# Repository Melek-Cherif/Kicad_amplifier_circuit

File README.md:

# Kicad_amplifier_circuit
 This repo contains a kicad project, which is also the assignement of Hardware design for Raspberry Pi course  from coursera

<div style="text-align: center;">
    
<div>

<div style="text-align: center;">
    
<div>

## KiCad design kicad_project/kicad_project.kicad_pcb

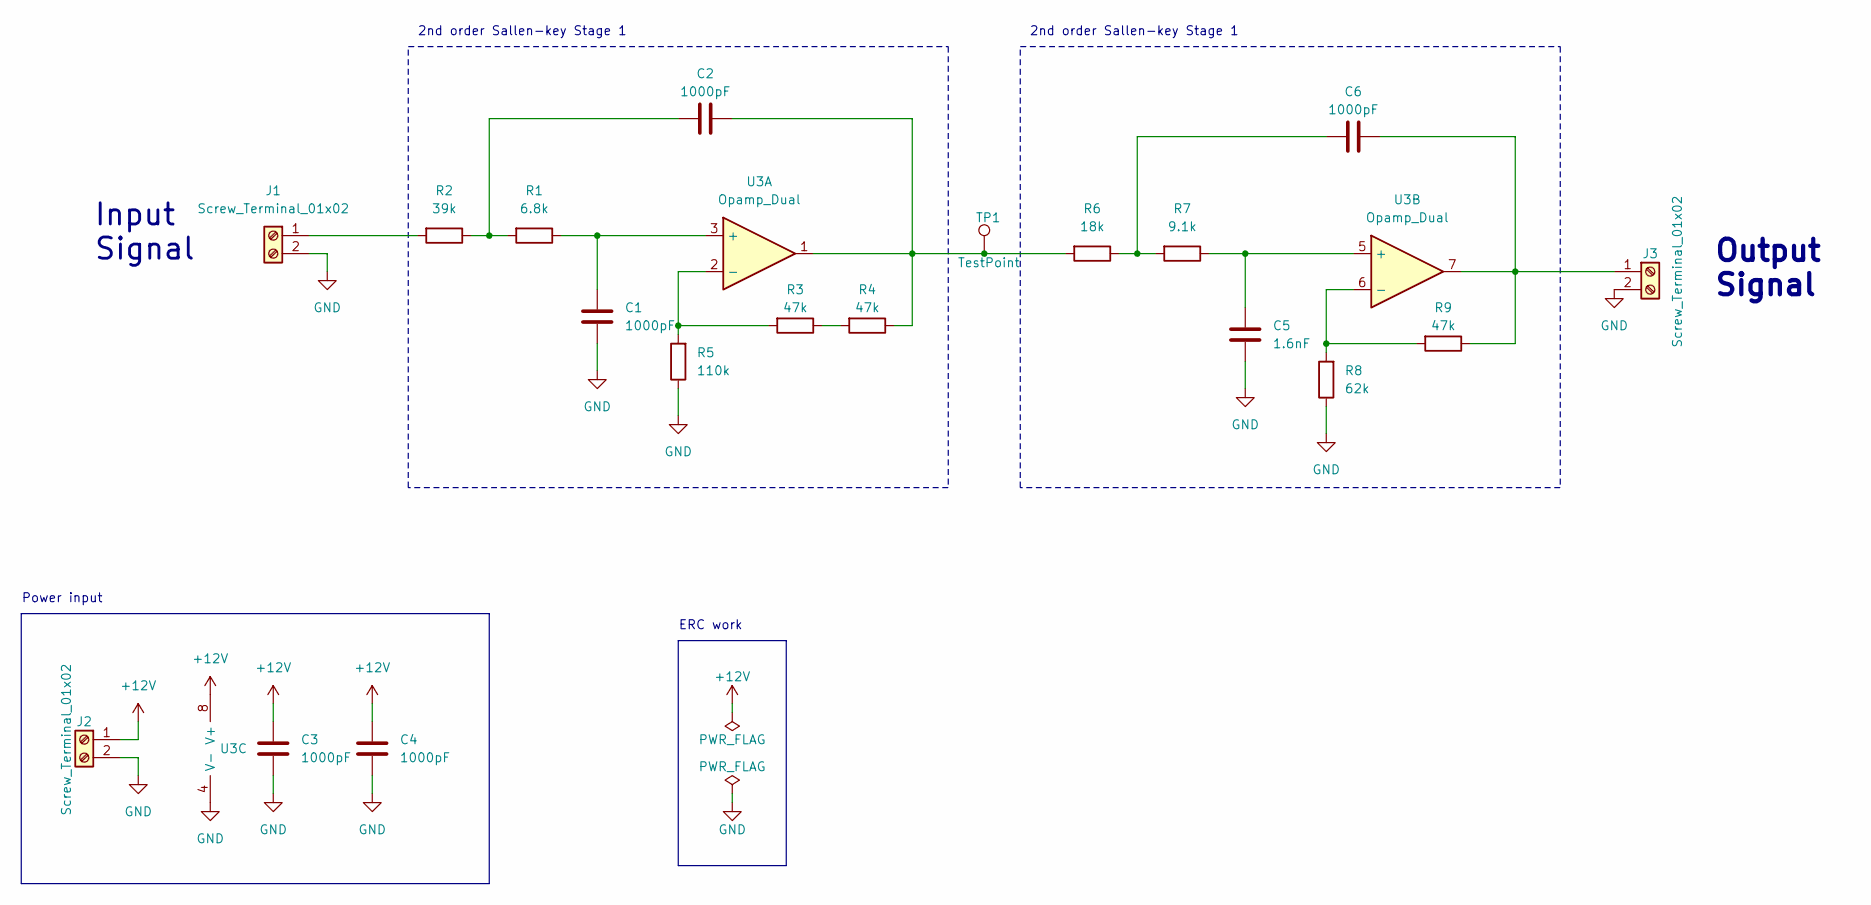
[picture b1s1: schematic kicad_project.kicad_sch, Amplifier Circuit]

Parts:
C1, C2, C3, C4, C6: 1000pF; CP_Radial_D4.0mm_P2.00mm
C5: 1.6nF; CP_Radial_D4.0mm_P2.00mm
J1, J2, J3: Screw_Terminal_01x02; PinHeader_1x02_P1.27mm_Vertical
R1: 6.8k; R_0402_1005Metric
R2: 39k; R_0402_1005Metric
R3, R4, R9: 47k; R_0402_1005Metric
R5: 110k; R_0402_1005Metric
R6: 18k; R_0402_1005Metric
R7: 9.1k; R_0402_1005Metric
R8: 62k; R_0402_1005Metric
TP1: TestPoint; TestPoint_Pad_2.0x2.0mm
U3: Opamp_Dual; DIP-8_W7.62mm

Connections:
+12V: C3.1, C4.1, J2.1, U3.8 (V+)
GND: C1.2, C3.2, C4.2, C5.2, J1.2, J2.2, J3.2, R5.1, R8.1, U3.4 (V-)
unnamed: C2.1, R4.1, R6.2, TP1.1, U3.1
unnamed: C2.2, R1.2, R2.1
unnamed: C6.2, R6.1, R7.2
unnamed: J1.1, R2.2
unnamed: C6.1, J3.1, R9.1, U3.7
unnamed: R3.1, R4.2
unnamed: C1.1, R1.1, U3.3 (+)
unnamed: R3.2, R5.2, U3.2 (-)
unnamed: C5.1, R7.1, U3.5 (+)
unnamed: R8.2, R9.2, U3.6 (-)

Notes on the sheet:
ERC work
2nd order Sallen-key Stage 1
Input Signal
Power input
Output Signal

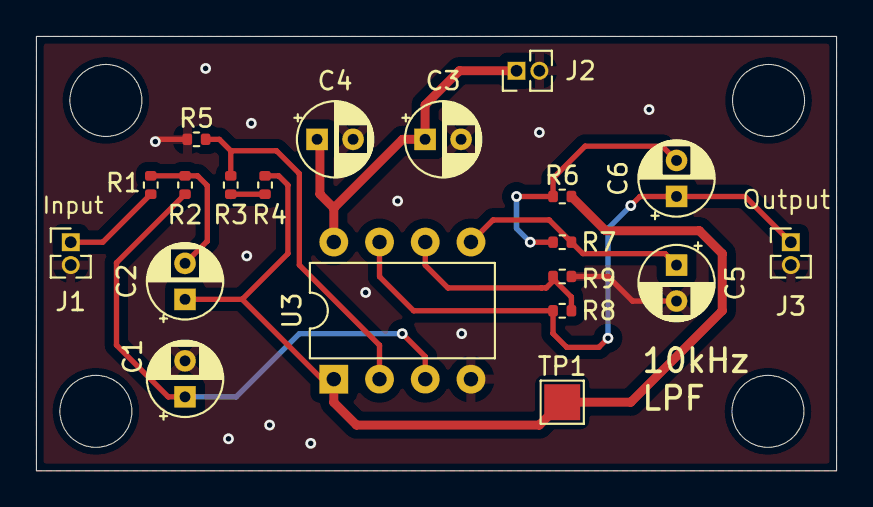
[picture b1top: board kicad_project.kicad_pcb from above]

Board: 2 copper layers, 44.5 x 24.1 mm, 20 parts (0 on the bottom side), 12 nets.

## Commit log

2024-09-24 init commit
2024-09-24 commit
    finish schematic
2024-09-24 commit
    Rule checker
2024-09-24 commit
    PCB setup
2024-09-25 commit
    finish PCB
2024-09-25 commit
    add images
2024-10-16 Update README.md
    add images
2024-10-16 export commit
